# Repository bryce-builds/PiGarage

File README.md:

# PiGarage

Open-source Raspberry Pi power management and audio HAT for automotive head-unit use.

## Features

- **5V 5A Buck Converter** (TPS54560BQDDARQ1) — 7-16V input, Pi 5 compatible
- **I2S DAC** (PCM5122PWR) — 112dB SNR, noise-free audio output to external amplifier
- **ADC** (ADS1115) — 16-bit, for steering wheel resistor ladder controls
- **4-Channel Optoisolated 12V Sensing** — ACC, REV, ILL, AUX via LTV-847S
- **Safe Shutdown** — ACC-triggered power latch with GPIO hold (BCM25), crank ride-through
- **Battery Protection** — UVLO hard cutoff at 12.08V via TL431A comparator
- **Fan Output** — JST SH 1.0mm 2-pin connector (Pi 5 fan style) for 25mm buck cooler fan
- **Compatible** — Raspberry Pi 3, 4, and 5

## Board

| Parameter | Value |
|-----------|-------|
| Input Voltage | 7-16V (automotive 12V) |
| Output Voltage | 5.0V |
| Output Current | 5A continuous |
| DAC SNR | 112dB |
| DAC Interface | I2S |
| ADC Resolution | 16-bit, 4-channel |
| Sense Inputs | 4ch optoisolated |
| Board Format | Raspberry Pi HAT (65mm x 56.5mm) |

## Directory Layout

```
PiGarage/
├── Hardware/           KiCad 10 schematic, PCB, and custom libraries
├── Production/         Gerbers, drill files, pick-and-place
├── BOM/                Bill of Materials and design notes
├── Images/             Board renders and schematic exports
├── Cover/              3D-printable enclosure / fan cover (STEP/STL)
├── Software/           Power latch daemon and systemd service
└── Docs/               Ordering and assembly guide
```

## Getting Started

See [Docs/ordering-guide.md](Docs/ordering-guide.md) for full instructions on ordering from JLCPCB and assembling the board.

## License

Hardware: [CERN-OHL-S-2.0](https://ohwr.org/cern_ohl_s_v2.txt) — Software: MIT

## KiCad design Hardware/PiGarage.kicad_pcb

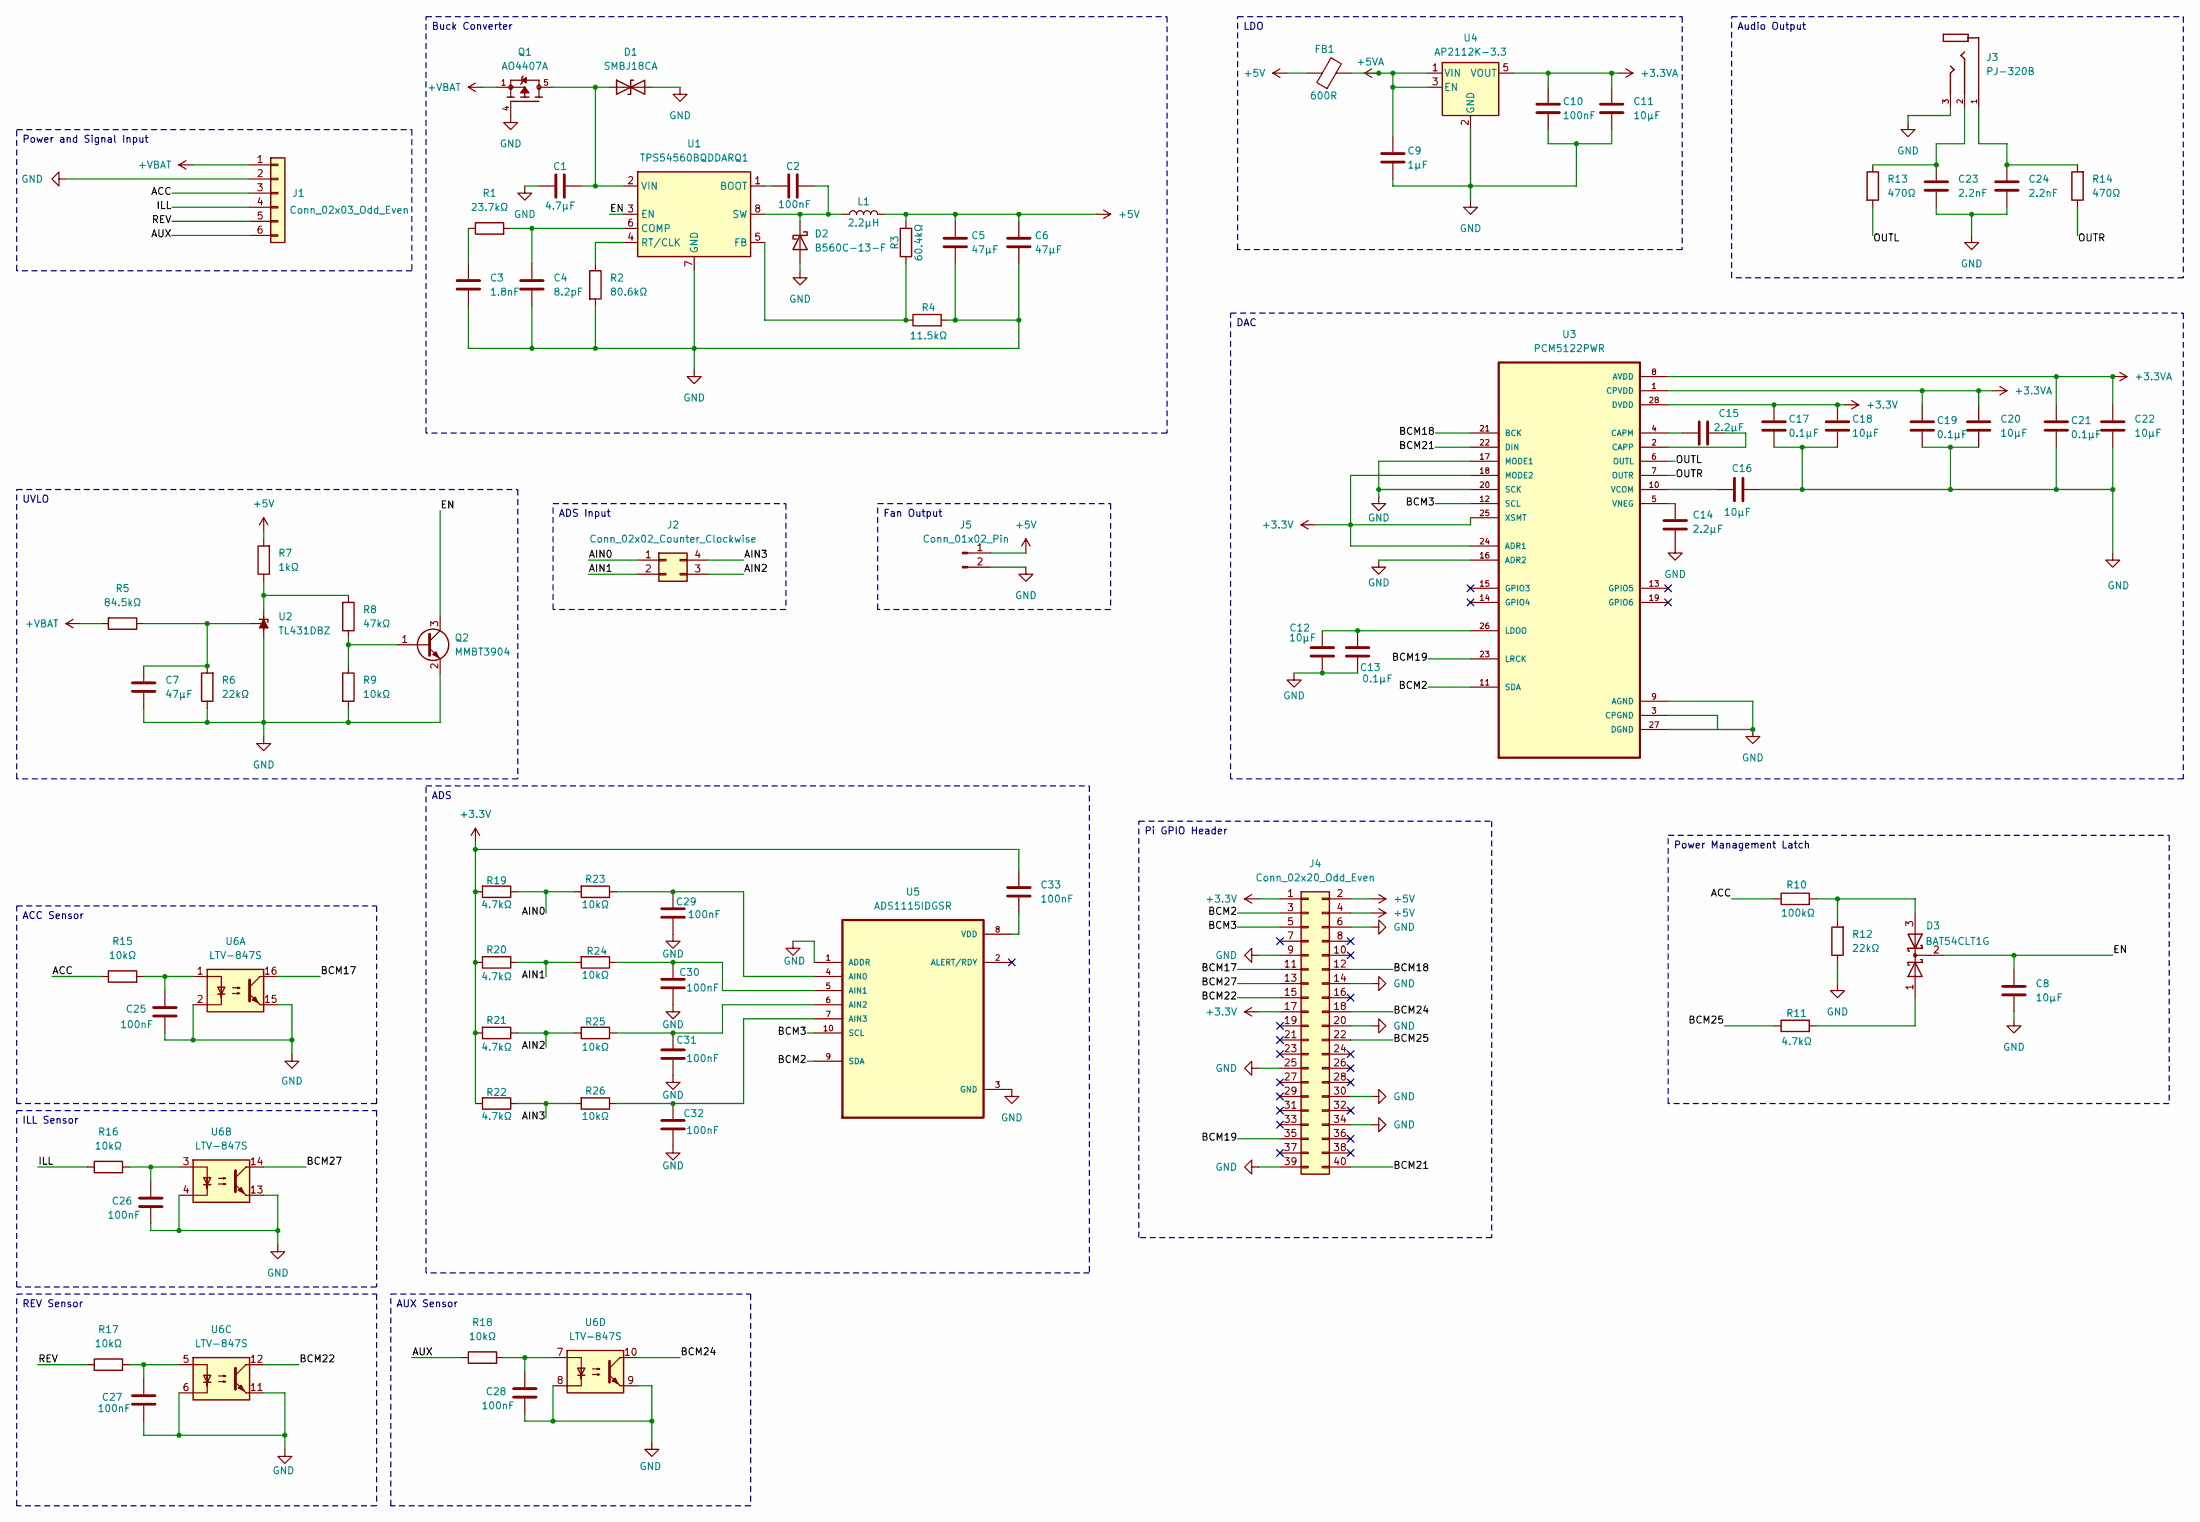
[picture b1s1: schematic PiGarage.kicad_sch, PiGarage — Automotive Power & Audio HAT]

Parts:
C1: 4.7µF; C_1206_3216Metric
C2, C10, C25, C26, C27, C28, C29, C30, C31, C32, C33: 100nF; C_0603_1608Metric
C3: 1.8nF; C_0603_1608Metric
C4: 8.2pF; C_0603_1608Metric
C5, C6, C7: 47µF; C_1206_3216Metric
C8, C11, C12, C16, C18, C20, C22: 10µF; C_0603_1608Metric
C9: 1µF; C_0603_1608Metric
C13, C17, C19, C21: 0.1µF; C_0603_1608Metric; MPN CC0603KRX7R9BB104; LCSC C14663
C14, C15: 2.2µF; C_0603_1608Metric
C23, C24: 2.2nF; C_0603_1608Metric
D1: SMBJ18CA; D_SMB
D2: B560C-13-F; SMC_L7.1-W6.2-LS8.1-RD
D3: BAT54CLT1G; SOT-23
FB1: 600R; L_0603_1608Metric
J1: Conn_02x03_Odd_Even; Molex_Mini-Fit_Jr_5566-06A_2x03_P4.20mm_Vertical
J2: Conn_02x02_Counter_Clockwise; Molex_Mini-Fit_Jr_5566-04A_2x02_P4.20mm_Vertical
J3: PJ-320B; BOOMELE_PJ-320B; MPN PJ-320B
J4: Conn_02x20_Odd_Even; PinSocket_2x20_P2.54mm_Vertical
J5: Conn_01x02_Pin; JST_PH_B2B-PH-K_1x02_P2.00mm_Vertical
L1: 2.2µH; IND-SMD_L7.0-W6.6
Q1: AO4407A; SOIC127P600X175-8N; PARTREV I
Q2: MMBT3904; TSOT-23
R1: 23.7kΩ; R_0603_1608Metric
R2: 80.6kΩ; R_0603_1608Metric
R3: 60.4kΩ; R_0603_1608Metric
R4: 11.5kΩ; R_0603_1608Metric
R5: 84.5kΩ; R_0603_1608Metric; MPN 0603WAF8452T5E; LCSC C23118
R6, R12: 22kΩ; R_0603_1608Metric; MPN 0603WAF2202T5E; LCSC C31850
R7: 1kΩ; R_0603_1608Metric; MPN 0603WAF1001T5E; LCSC C21190
R8: 47kΩ; R_0603_1608Metric; MPN 0603WAF4702T5E; LCSC C25819
R9, R15, R16, R17, R18, R23, R24, R25, R26: 10kΩ; R_0603_1608Metric; MPN 0603WAF1002T5E; LCSC C25804
R10: 100kΩ; R_0603_1608Metric; MPN 0603WAF1003T5E; LCSC C25803
R11, R19, R20, R21, R22: 4.7kΩ; R_0603_1608Metric; MPN 0603WAF4701T5E; LCSC C23162
R13, R14: 470Ω; R_0603_1608Metric; MPN 0603WAF4700T5E; LCSC C23179
U1: TPS54560BQDDARQ1; Texas_R-PDSO-G8_EP2.95x4.9mm_Mask2.4x3.1mm_ThermalVias
U2: TL431DBZ; SOT-23
U3: PCM5122PWR; TSSOP-28_4.4x9.7mm_P0.65mm
U4: AP2112K-3.3; SOT-23-5
U5: ADS1115IDGSR; SOP50P490X110-10N
U6: LTV-847S; SMDIP-16_W9.53mm

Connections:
+3.3V: C17.1, C18.2, C33.1, J4.1, J4.17, R19.2, R20.2, R21.2, R22.2, U3.18 (MODE2), U3.24 (ADR1), U3.25 (XSMT), U3.28 (DVDD)
+3.3VA: C10.2, C11.2, C19.1, C20.2, C21.1, C22.2, U3.1 (CPVDD), U3.8 (AVDD), U4.5 (VOUT)
+5V: C5.1, C6.1, FB1.1, J4.2, J4.4, J5.1, L1.2, R3.2, R7.2
+5VA: C9.1, FB1.2, U4.1 (VIN), U4.3 (EN)
+VBAT: J1.1, Q1.1, Q1.2, Q1.3, R5.2
/ACC: J1.3, R10.1, R15.1
/AIN0: J2.1, R19.1, R23.2
/AIN1: J2.2, R20.1, R24.2
/AIN2: J2.3, R21.1, R25.2
/AIN3: J2.4, R22.1, R26.2
/AUX: J1.6, R18.1
/BCM2: J4.3, U3.11 (SDA), U5.9 (SDA)
/BCM3: J4.5, U3.12 (SCL), U5.10 (SCL)
/BCM17: J4.11, U6.16
/BCM18: J4.12, U3.21 (BCK)
/BCM19: J4.35, U3.23 (LRCK)
/BCM21: J4.40, U3.22 (DIN)
/BCM22: J4.15, U6.12
/BCM24: J4.18, U6.10
/BCM25: J4.22, R11.1
/BCM27: J4.13, U6.14
/EN: C8.1, D3.2 (K), Q2.3 (C), U1.3 (EN)
/ILL: J1.4, R16.1
/OUTL: R13.2, U3.6 (OUTL)
/OUTR: R14.1, U3.7 (OUTR)
/REV: J1.5, R17.1
GND: C1.2, C3.2, C4.2, C5.2, C6.2, C7.1, C8.2, C9.2, C10.1, C11.1, C12.1, C13.1, C14.2, C16.1, C17.2, C18.1, C19.2, C20.1, C21.2, C22.1, C23.1, C24.2, C25.2, C26.2, C27.2, C28.2, C29.1, C30.2, C31.2, C32.2, D1.2 (A2), D2.2 (A), J1.2, J3.3, J4.6, J4.9, J4.14, J4.20, J4.25, J4.30, J4.34, J4.39, J5.2, Q1.4, Q2.2 (E), R2.2, R4.2, R6.1, R9.2, R12.1, U1.7 (GND), U1.9 (GND), U2.3 (A), U3.9 (AGND), U3.16 (ADR2), U3.17 (MODE1), U3.20 (SCK), U3.27 (DGND), U4.2 (GND), U5.1 (ADDR), U5.3 (GND), U6.2, U6.4, U6.6, U6.8, U6.9, U6.11, U6.13, U6.15
unnamed: C3.1, R1.1
unnamed: C23.2, J3.2, R13.1
unnamed: C24.1, J3.1, R14.2
unnamed: C25.1, R15.2, U6.1
unnamed: C26.1, R16.2, U6.3
unnamed: C27.1, R17.2, U6.5
unnamed: C28.1, R18.2, U6.7
unnamed: C1.1, D1.1 (A1), Q1.5, Q1.6, Q1.7, Q1.8, U1.2 (VIN)
unnamed: C2.2, D2.1 (K), L1.1, U1.8 (SW)
unnamed: D3.1 (A), R11.2
unnamed: D3.3 (A), R10.2, R12.2
unnamed: Q2.1 (B), R8.2, R9.1
unnamed: C2.1, U1.1 (BOOT)
unnamed: C4.1, R1.2, U1.6 (COMP)
unnamed: R3.1, R4.1, U1.5 (FB)
unnamed: R2.1, U1.4 (RT/CLK)
unnamed: R7.1, R8.1, U2.1 (K)
unnamed: C7.2, R5.1, R6.2, U2.2 (REF)
unnamed: C15.2, U3.4 (CAPM)
unnamed: C15.1, U3.2 (CAPP)
unnamed: C12.2, C13.2, U3.26 (LDOO)
unnamed: C16.2, U3.10 (VCOM)
unnamed: C14.1, U3.5 (VNEG)
unnamed: C29.2, R23.1, U5.4 (AIN0)
unnamed: C30.1, R24.1, U5.5 (AIN1)
unnamed: C31.1, R25.1, U5.6 (AIN2)
unnamed: C32.1, R26.1, U5.7 (AIN3)
unnamed: C33.2, U5.8 (VDD)

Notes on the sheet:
Power Management Latch
Buck Converter
AUX Sensor
REV Sensor
DAC
LDO
ILL Sensor
ADS
Fan Output
ADS Input
Power and Signal Input
ACC Sensor
Pi GPIO Header
UVLO
Audio Output

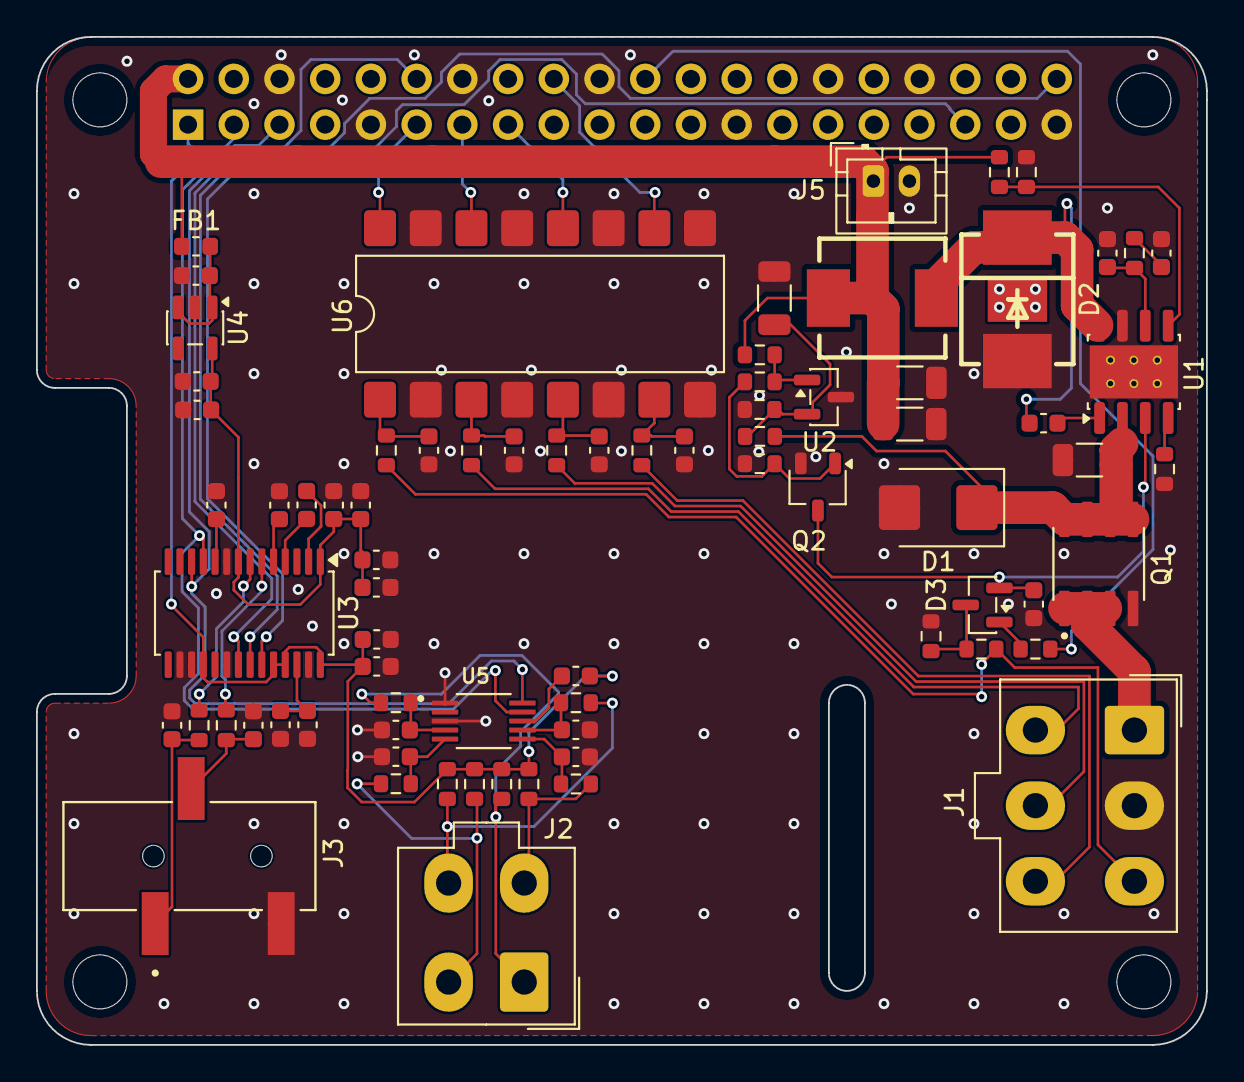
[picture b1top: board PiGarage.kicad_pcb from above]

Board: 2 copper layers, 65.0 x 56.0 mm, 77 parts (1 on the bottom side), 55 nets.

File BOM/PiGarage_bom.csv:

Reference,Qty,Value,Footprint,MPN,Manufacturer,LCSC,LC_Stock,Chosen_Distributor,Datasheet,Validated,DNP,Notes
C1,1,4.7µF,1206,,,,,,,,,
C3,1,1.8nF,0603,,,,,,,,,
C4,1,8.2pF,0603,,,,,,,,,
"C5,C6,C7",3,47µF,1206,,,,,,,,,
C9,1,1µF,0603,,,,,,,,,
"C11,C8,C22,C12,C18,C20,C16",7,10µF,0603,,,,,,,,,
"C15,C14",2,2.2µF,0603,,,,,,,,,
"C21,C13,C17,C19",4,0.1µF,0603,CC0603KRX7R9BB104,Yageo,C14663,,,,,,
"C23,C24",2,2.2nF,0603,,,,,,,,,
"C32,C2,C25,C31,C27,C33,C28,C10,C30,C26,C29",11,100nF,0603,,,,,,,,,
D1,1,SMBJ18CA,SMB,,,,,,,,,
D2,1,B560C-13-F,SMC_L7.1-W6.2-LS8.1-RD,,,,,,,,,
D3,1,BAT54CLT1G,SOT-23,,,,,,,,,
FB1,1,600R,0603,,,,,,,,,
J1,1,Conn_02x03_Odd_Even,Molex_Mini-Fit_Jr_5566-06A_2x03_P4.20mm_Vertical,1724470206,Molex,,,,,,,
J2,1,Conn_02x02_Counter_Clockwise,Molex_Mini-Fit_Jr_5566-04A_2x02_P4.20mm_Vertical,1724470204,Molex,,,,,,,
J3,1,PJ-320B,BOOMELE_PJ-320B,PJ-320B,Luoyang Dishang electronics,,,,,,,
J4,1,Conn_02x20_Odd_Even,PinSocket_2x20_P2.54mm_Vertical,,,,,,,,,
L1,1,2.2µH,IND-SMD_L7.0-W6.6,,,,,,,,,
Q1,1,AO4407A,SOIC127P600X175-8N,,,,,,,,,
Q2,1,MMBT3904,TSOT-23,,,,,,https://www.onsemi.com/pdf/datasheet/pzt3904-d.pdf,,,
R1,1,23.7kΩ,0603,,,,,,,,,
R2,1,80.6kΩ,0603,,,,,,,,,
R3,1,60.4kΩ,0603,,,,,,,,,
R4,1,11.5kΩ,0603,,,,,,,,,
R5,1,84.5kΩ,0603,0603WAF8452T5E,UNI-ROYAL(Uniroyal Elec),C23118,,,,,,
"R6,R12",2,22kΩ,0603,0603WAF2202T5E,UNI-ROYAL(Uniroyal Elec),C31850,,,,,,
R7,1,1kΩ,0603,0603WAF1001T5E,UNI-ROYAL(Uniroyal Elec),C21190,,,,,,
R8,1,47kΩ,0603,0603WAF4702T5E,UNI-ROYAL(Uniroyal Elec),C25819,,,,,,
R10,1,100kΩ,0603,0603WAF1003T5E,UNI-ROYAL(Uniroyal Elec),C25803,,,,,,
"R13,R14",2,470Ω,0603,0603WAF4700T5E,UNI-ROYAL(Uniroyal Elec),C23179,,,,,,
"R18,R15,R16,R23,R9,R17,R26,R24,R25",9,10kΩ,0603,0603WAF1002T5E,UNI-ROYAL(Uniroyal Elec),C25804,,,,,,
"R20,R19,R22,R11,R21",5,4.7kΩ,0603,0603WAF4701T5E,UNI-ROYAL(Uniroyal Elec),C23162,,,,,,
U1,1,TPS54560BQDDARQ1,Texas_R-PDSO-G8_EP2.95x4.9mm_Mask2.4x3.1mm_ThermalVias,,,,,,https://www.ti.com/lit/ds/symlink/tps54560b.pdf,,,
U2,1,TL431DBZ,SOT-23,,,,,,http://www.ti.com/lit/ds/symlink/tl431.pdf,,,
U3,1,PCM5122PWR,TSSOP-28_4.4x9.7mm_P0.65mm,,,,,,,,,
U4,1,AP2112K-3.3,SOT-23-5,,,,,,https://www.diodes.com/assets/Datasheets/AP2112.pdf,,,
U5,1,ADS1115IDGSR,SOP50P490X110-10N,,,,,,,,,
U6,1,LTV-847S,SMDIP-16_W9.53mm,,,,,,http://www.us.liteon.com/downloads/LTV-817-827-847.PDF,,,

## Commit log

2026-05-13 Add J5 JST SH 1.0mm fan output connector
    Adds a 2-pin JST SH 1.0mm (BM02B-SRSS-TB) fan power header to the schematic.
    Pin 1 = +5V, Pin 2 = GND. Taps the unfiltered 5V rail near U1 (buck converter)
    for a 25mm cooling fan. Same connector family as the RPi 5 fan.
    Updated docs: README features list, BOM/design-notes.txt (new J5 section,
    hand-solder list), and Docs/ordering-guide.md (hand-solder step).
2026-05-14 Swap J5 fan connector: JST SH 1.0mm SMD → JST PH 2.0mm through-hole
    B2B-PH-K-S (C131337) replaces BM02B-SRSS-TB. Through-hole, keyed,
    locking tab — better suited to automotive vibration. Relocated J5
    near U1/L1 so fan sits directly over the buck converter hotspot.
    Mating: PHR-2 housing + SPH-002T-P0.5L contacts.
    Updated schematic footprint, PCB layout, BOM design-notes, and
    ordering guide. Notes that C131337 is Extended (~$3 fee) so
2026-05-21 Fix J1/J2 Molex MPNs to 172447 series (4.2x5.5mm pin spacing)
2026-05-21 Update J1/J2 Molex MPNs to 172447 series
2026-05-21 Fix J1/J2/J4 connector references in ordering guide
2026-05-21 Add DigiKey links for GPIO header, fan, standoffs, screws
2026-05-21 Add wire-side harness and accessories section with DigiKey links
2026-05-21 Update screw qty to 7 (4 HAT + 3 fan)
2026-05-21 Add board with cover render
2026-05-21 Add board-cover image to README
2026-05-21 Update Front board render
2026-05-21 Update Back board render
2026-05-21 Add Cover folder with board reference STEP for enclosure design
2026-05-21 Add Cover/ to directory layout
2026-05-21 Update board-cover render
2026-05-24 Standoffs: 8mm → 11mm to match GPIO header height

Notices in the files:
Hardware/PiGarage.kicad_pcb:
License: CERN-OHL-S-2.0
